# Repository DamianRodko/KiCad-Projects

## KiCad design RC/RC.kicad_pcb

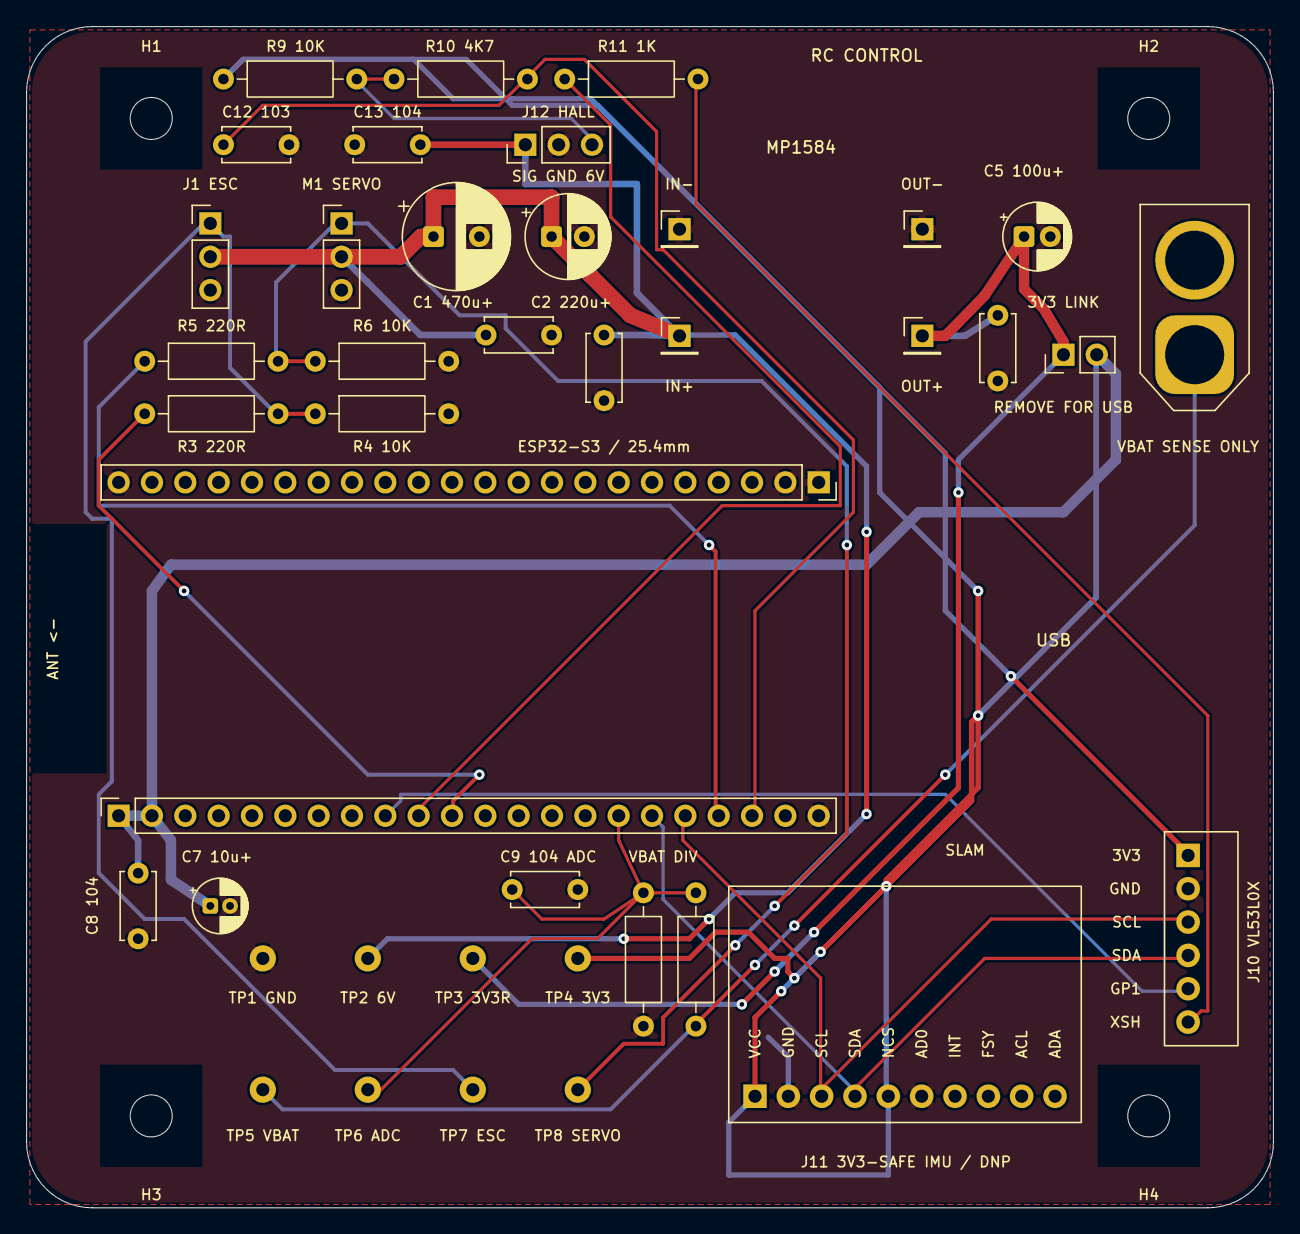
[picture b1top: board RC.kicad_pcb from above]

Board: 2 copper layers, 95.0 x 90.0 mm, 45 parts (0 on the bottom side), 17 nets.

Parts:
C1: 470uF 16V; CP_Radial_D8.0mm_P3.50mm
C2: 220uF 25V; CP_Radial_D6.3mm_P2.50mm
C3, C4, C6, C8, C9, C13: 100nF 50V; C_Disc_D5.0mm_W2.5mm_P5.00mm
C5: 100uF 16V; CP_Radial_D5.0mm_P2.00mm
C7: 10uF 25V; CP_Radial_D4.0mm_P1.50mm
C12: 10nF 50V; C_Disc_D5.0mm_W2.5mm_P5.00mm
H1, H2, H3, H4: M3; MountingHole_3.2mm_M3
J1: BEC; PinHeader_1x03_P2.54mm_Vertical
J2: ESP32L; PinSocket_1x22_P2.54mm_Vertical
J3: ESP32R; PinSocket_1x22_P2.54mm_Vertical
J4: BuckIn-; PinHeader_1x01_P2.54mm_Vertical
J5: BuckIn+; PinHeader_1x01_P2.54mm_Vertical
J6: BuckOut-; PinHeader_1x01_P2.54mm_Vertical
J7: BuckOut+; PinHeader_1x01_P2.54mm_Vertical
J8: VBAT_SENSE_IN; AMASS_XT60-M_1x02_P7.20mm_Vertical
J9: 3V3 LINK; PinHeader_1x02_P2.54mm_Vertical
J10: CJVL53L0XV2; CJVL53L0XV2_RightAngle_1x06_P2.54mm
J11: CJMCU-20948; CJMCU-20948_Socket_1x10_P2.54mm
J12: A3144 REMOTE; PinHeader_1x03_P2.54mm_Vertical
M1: MG90; PinHeader_1x03_P2.54mm_Vertical
R1: 100k; R_Axial_DIN0207_L6.3mm_D2.5mm_P10.16mm_Horizontal
R2: 330k; R_Axial_DIN0207_L6.3mm_D2.5mm_P10.16mm_Horizontal
R3, R5: 220R; R_Axial_DIN0207_L6.3mm_D2.5mm_P10.16mm_Horizontal
R4, R6, R9: 10k; R_Axial_DIN0207_L6.3mm_D2.5mm_P10.16mm_Horizontal
R10: 4.7k; R_Axial_DIN0207_L6.3mm_D2.5mm_P10.16mm_Horizontal
R11: 1k; R_Axial_DIN0207_L6.3mm_D2.5mm_P10.16mm_Horizontal
TP1: GND; TestPoint_THT_D2_Drill1
TP2: 6V; TestPoint_THT_D2_Drill1
TP3: 3V3 RAW; TestPoint_THT_D2_Drill1
TP4: 3V3; TestPoint_THT_D2_Drill1
TP5: VBAT; TestPoint_THT_D2_Drill1
TP6: VBAT SENSE; TestPoint_THT_D2_Drill1
TP7: ESC PWM; TestPoint_THT_D2_Drill1
TP8: SERVO PWM; TestPoint_THT_D2_Drill1

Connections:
+3.3V: C7.1, C8.1, J2.1, J2.2, J9.2, J10.1, J11.1, J11.5, R9.1, TP4.1
+6V: C1.1, C2.1, C3.1, C4.1, C13.1, J1.2, J5.1 (Pin_1_1), J12.1, M1.2 (+), TP2.1
/BUCK_3V3_RAW: C5.1, C6.1, J7.1 (Pin_1_1), J9.1, TP3.1
/HALL_RAW: J12.3, R9.2, R10.1
/IO11: J2.17, J10.4, J11.4
/IO12: J2.18, J10.3, J11.3
/IO14: C12.1, J2.20, R10.2
/IO16: J2.9, J10.5
/IO17: J2.10, R11.1
/PWM_ESC: J2.11, R3.1
/PWM_ESC_OUT: J1.1, R3.2, R4.1, TP7.1
/PWM_SERVO: J2.19, R5.1
/PWM_SERVO_OUT: M1.1 (PWM), R5.2, R6.1, TP8.1
/VBAT: J8.1, R2.2, TP5.1
/VBAT_SENSE: C9.1, J2.16, R1.1, R2.1, TP6.1
/VL_XSHUT: J10.6, R11.2
GND: C1.2, C2.2, C3.2, C4.2, C5.2, C6.2, C7.2, C8.2, C9.2, C12.2, C13.2, J1.3, J2.22, J3.1, J3.2, J3.22, J4.1 (Pin_1_1), J6.1 (Pin_1_1), J8.2, J10.2, J11.2, J11.6, J12.2, M1.3 (-), R1.2, R4.2, R6.2, TP1.1
